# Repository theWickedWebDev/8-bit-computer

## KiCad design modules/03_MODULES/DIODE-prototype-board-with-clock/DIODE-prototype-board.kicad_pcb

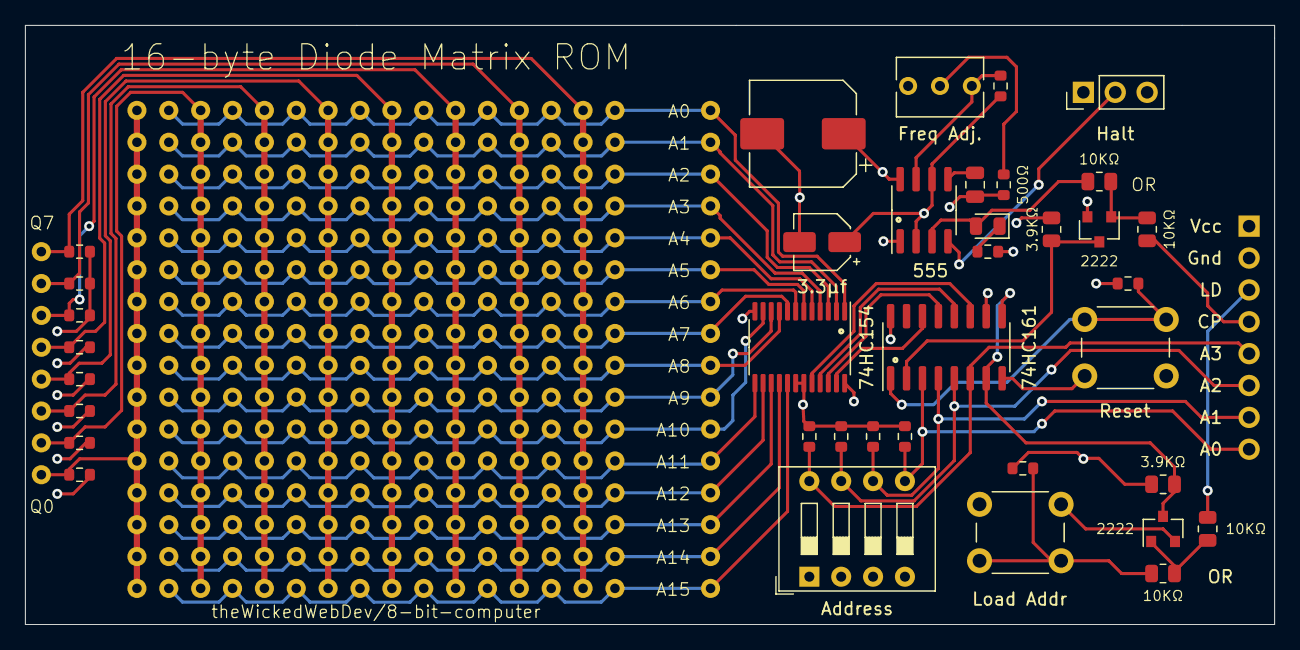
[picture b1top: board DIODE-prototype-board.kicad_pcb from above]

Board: 4 copper layers, 99.6 x 47.8 mm, 39 parts (1 on the bottom side), 49 nets.

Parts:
C1: C; C_0805_2012Metric
C2: CP1; CP_Elec_4x4.5
C3: CP1; CP_Elec_8x10
D1: LED; LED_0805_2012Metric
J1: Conn_01x08; PinHeader_1x08_P2.54mm_Vertical
Q1, Q2: PMBT2222; SOT-23
R1, R2, R3, R4, R5, R6, R7, R8, R9, R10, R11, R12, R13, R14, R15, R16, R17: R_US; R_0603_1608Metric
R18, R19, R21, R22: 10kohm; R_0805_2012Metric
R20, R23: 3.9kohm; R_0805_2012Metric
RV2: 3296W-1-203; Potentiometer_Bourns_3266Y_Vertical
SW1: SW_SPDT; PinHeader_1x03_P2.54mm_Vertical
SW2, SW4: SW_Push; SW_PUSH_6mm
SW3: SW_DIP_x04; SW_DIP_SPSTx04_Slide_9.78x12.34mm_W7.62mm_P2.54mm
U1: diode-matrix-8x16; diode-array-sockets
U2: TLC555xD; SOIC-8_3.9x4.9mm_P1.27mm
U3: 74LS154; TSSOP-24_4.4x7.8mm_P0.65mm
U4: 74LS161; SOIC-16_3.9x9.9mm_P1.27mm

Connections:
AUTO_CLOCK: D1.2, R18.1, U2.3
CLOCK: Q1.3, R20.2, U4.2
EXT_CLOCK: J1.4, R19.1
EXT_LOAD: J1.3, R21.1
GND: C2.2, C3.2, J1.2, Q1.2, Q2.2, R13.1, R14.1, R15.1, R16.1, R17.2, SW1.3, SW2.2, SW4.2, U2.1, U3.12, U3.18, U3.19, U4.8
LOAD: Q2.3, R23.2, U4.7, U4.9
unnamed: C1.1, U2.5
unnamed: C2.1, R5.2, U2.2, U2.6
unnamed: D1.1, R17.1
unnamed: J1.5, R16.2, SW3.8, U4.6
unnamed: J1.6, R15.2, SW3.7, U4.5
unnamed: J1.7, R14.2, SW3.6, U4.4
unnamed: J1.8, R13.2, SW3.5, U4.3
unnamed: Q1.1, R18.2, R19.2
unnamed: Q2.1, R21.2, R22.2
unnamed: R1.1, U1.1
unnamed: R2.1, U1.2
unnamed: R3.1, U1.3
unnamed: R4.1, U1.4
unnamed: R5.1, RV2.1, U2.7
unnamed: R6.1, U1.5
unnamed: R7.1, U1.6
unnamed: R8.1, U1.7
unnamed: R9.1, U1.8
unnamed: R10.1, RV2.2
unnamed: R11.1, SW2.1, U4.1
unnamed: R12.1, R22.1, SW4.1
unnamed: SW1.2, U2.4
unnamed: U1.9, U3.1
unnamed: U1.10, U3.2
unnamed: U1.11, U3.3
unnamed: U1.12, U3.4
unnamed: U1.13, U3.5
unnamed: U1.14, U3.6
unnamed: U1.15, U3.7
unnamed: U1.16, U3.8
unnamed: U1.17, U3.9
unnamed: U1.18, U3.10
unnamed: U1.19, U3.11
unnamed: U1.20, U3.13
unnamed: U1.21, U3.14
unnamed: U1.22, U3.15
unnamed: U1.23, U3.16
unnamed: U1.24, U3.17
unnamed: U3.20, U4.11
unnamed: U3.21, U4.12
unnamed: U3.22, U4.13
unnamed: U3.23, U4.14
VCC: C1.2, C3.1, J1.1, R1.2, R2.2, R3.2, R4.2, R6.2, R7.2, R8.2, R9.2, R10.2, R11.2, R12.2, R20.1, R23.1, SW1.1, SW3.1, SW3.2, SW3.3, SW3.4, U2.8, U3.24, U4.10, U4.16

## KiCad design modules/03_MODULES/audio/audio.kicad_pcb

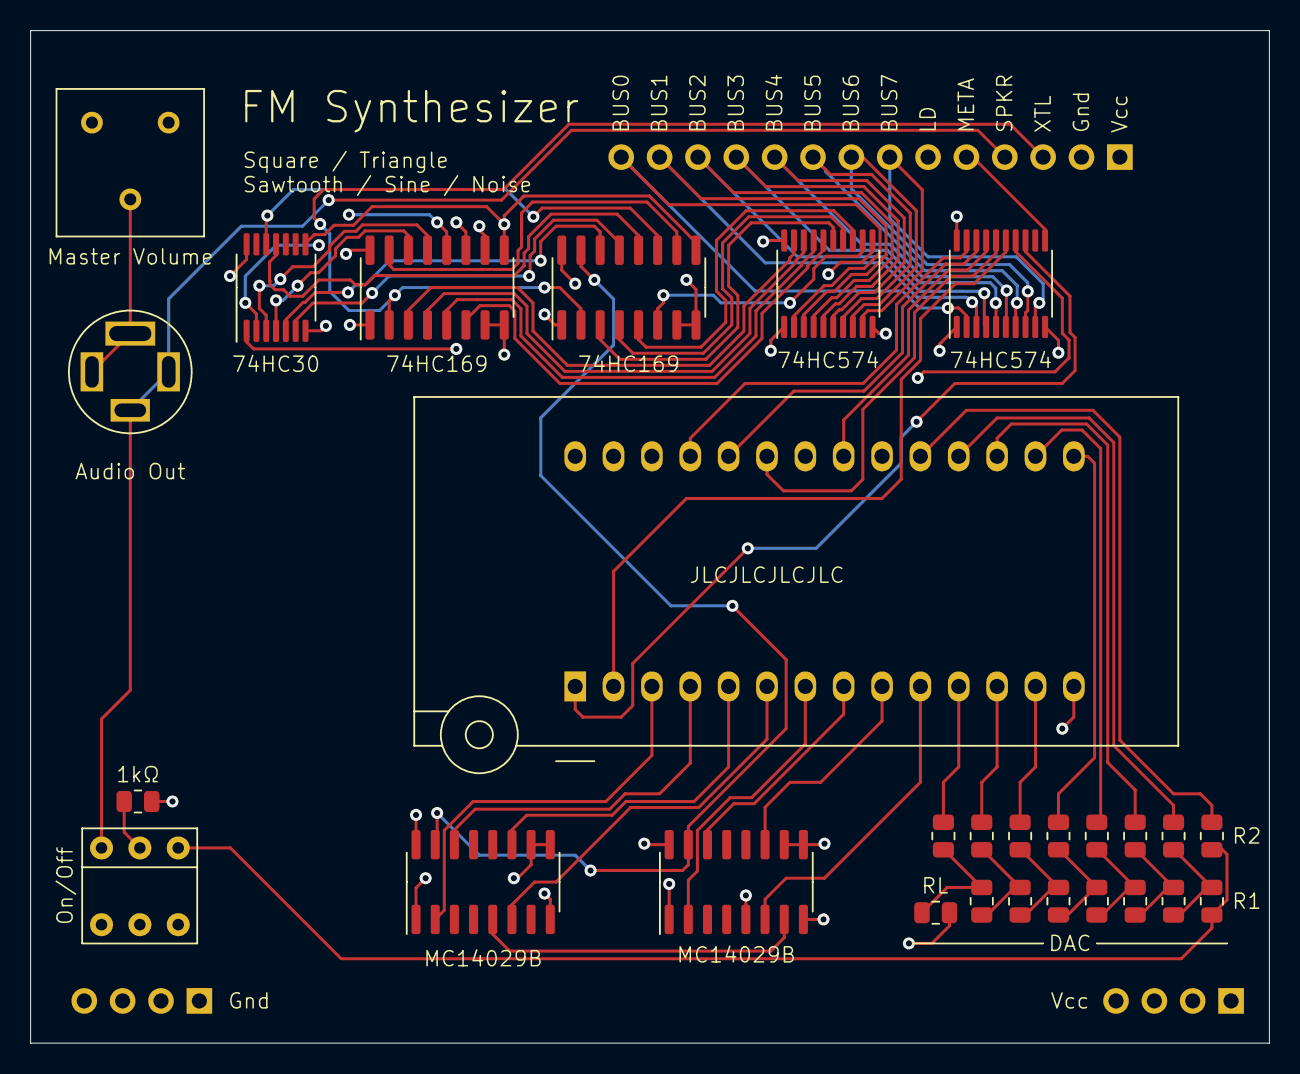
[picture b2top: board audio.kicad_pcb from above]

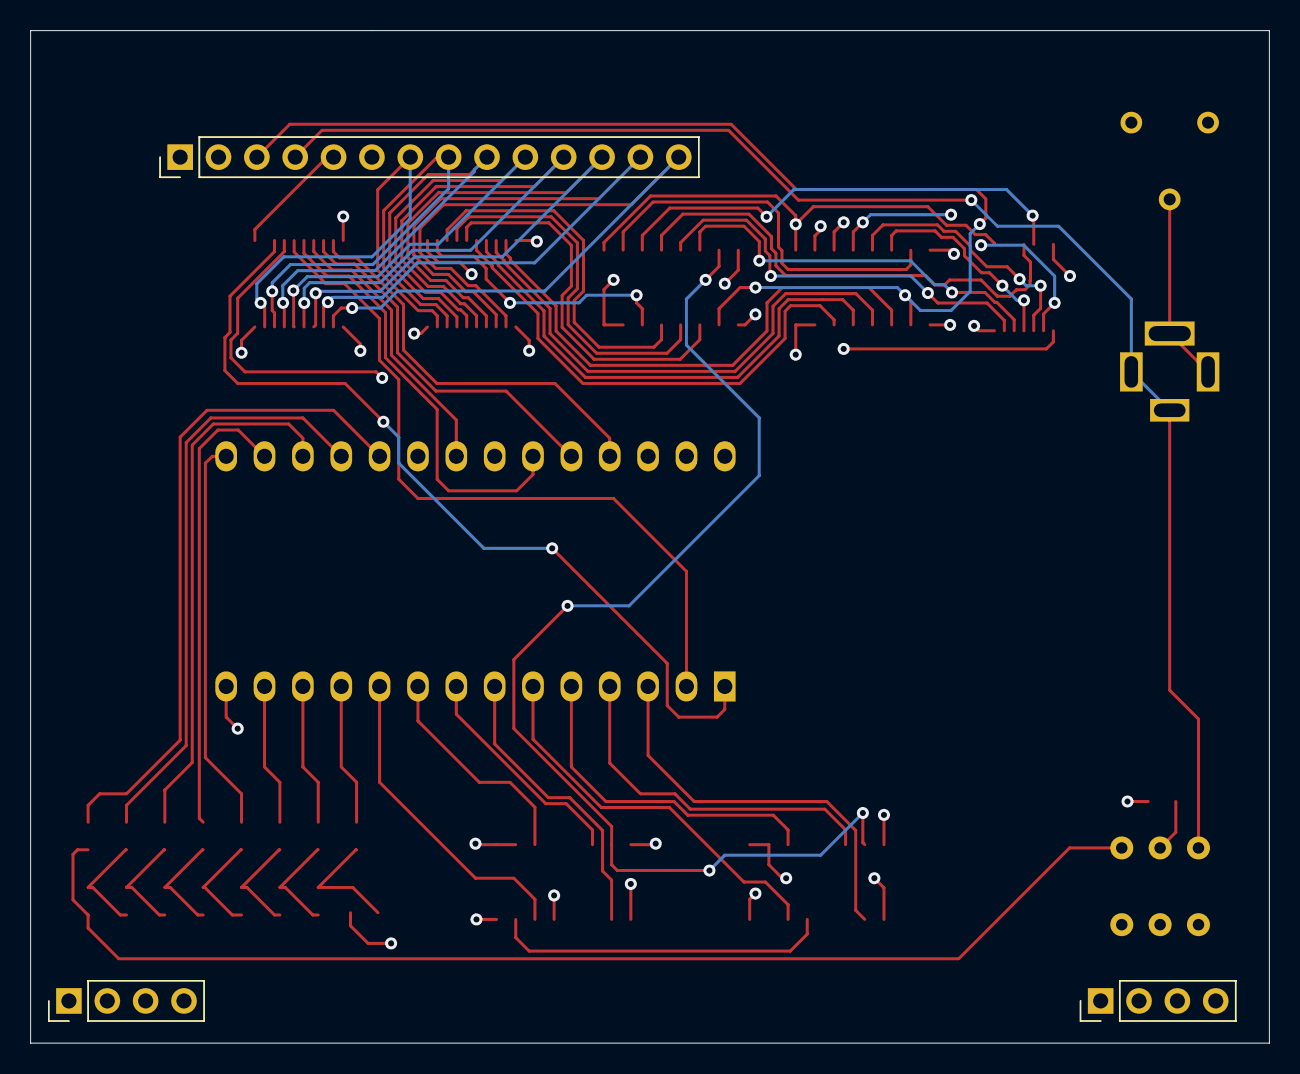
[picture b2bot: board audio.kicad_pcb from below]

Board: 4 copper layers, 82.0 x 67.1 mm, 31 parts (3 on the bottom side), 67 nets.

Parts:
J1: Conn_01x14; PinHeader_1x14_P2.54mm_Vertical
J3, J4: Conn_01x04; PinHeader_1x04_P2.54mm_Vertical
LS1: Speaker; 3.5mm_Audio_Jack-STEPHEN
R1, R2, R3, R4, R5, R6, R7, R8, R9, R10, R11, R12, R13, R14, R15, R16, R17: R_US; R_0805_2012Metric
RV1: R_POT_TRIM_US; Potentiometer_Bourns_3386F_Vertical
SW1: SW_DPDT_x2; THT-DPDT
U1, U2: 74LS574; TSSOP-20_4.4x6.5mm_P0.65mm
U3, U7: 74LS169; SOIC-16_3.9x9.9mm_P1.27mm
U4, U6: MC14029B; SOIC-16_3.9x9.9mm_P1.27mm
U5: 74LS30; TSSOP-14_4.4x5mm_P0.65mm
U8: 28C256; DIP_Socket-28_W11.9_W12.7_W15.24_W17.78_W18.5_3M_228-1277-0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

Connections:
/D1: R3.1, U8.12
/D2: R5.1, U8.13
/D3: R7.1, U8.15
/D4: R9.1, U8.16
/D5: R11.1, U8.17
/D6: R13.1, U8.18
/D7: R15.1, U8.19
/DO: R1.1, U8.11
/QDIVISION0: U2.19, U3.3
/QDIVISION1: U2.18, U3.4
/QDIVISION2: U2.17, U3.5
/QDIVISION3: U2.16, U3.6
/QDIVISION4: U2.15, U7.3
/QDIVISION5: U2.14, U7.4
/QDIVISION6: U2.13, U7.5
/QDIVISION7: U2.12, U7.6
A0: U4.6, U8.10
A1: U4.11, U8.9
A2: U4.14, U8.8
A3: U4.2, U8.7
A4: U6.6, U8.6
A5: U6.11, U8.5
A6: U6.14, U8.4
A7: U6.2, U8.3
A8: U1.19, U8.25
A9: U1.18, U8.24
A10: U1.17, U8.21
A11: U1.16, U8.23
A12: U1.15, U8.2
A13: U1.14, U8.26
A14: U1.13, U8.1
CRYSTAL_OSCILLATOR_IN: J1.3, U3.2, U7.2
DATABUS0: J1.14, U1.2, U2.2
DATABUS1: J1.13, U1.3, U2.3
DATABUS2: J1.12, U1.4, U2.4
DATABUS3: J1.11, U1.5, U2.5
DATABUS4: J1.10, U1.6, U2.6
DATABUS5: J1.9, U1.7, U2.7
DATABUS6: J1.8, U1.8, U2.8
DATABUS7: J1.7, U1.9, U2.9
FREQ0: U3.14, U5.4
FREQ1: U3.13, U5.3
FREQ2: U3.12, U5.2
FREQ3: U3.11, U5.1
FREQ4: U5.5, U7.14
FREQ5: U5.6, U7.13
FREQ6: U5.11, U7.12
FREQ7: U5.12, U7.11
FREQUENCY_CLOCK_PULSE: U4.15, U6.15, U7.15
GND: J1.2, J4.1, J4.2, J4.3, J4.4, R16.2, R17.1, RV1.3, U1.1, U1.10, U2.1, U2.10, U3.1, U3.7, U3.8, U3.10, U4.1, U4.5, U4.8, U5.7, U6.1, U6.8, U7.1, U7.7, U7.8, U8.14, U8.20, U8.22
LOAD_DIVISION: J1.6, U2.11
LOAD_META: J1.5, U1.11
unnamed: LS1.R1, LS1.R2, RV1.2
unnamed: R1.2, R2.2, R16.1
unnamed: R2.1, R3.2, R4.2
unnamed: R4.1, R5.2, R6.2
unnamed: R6.1, R7.2, R8.2
unnamed: R10.1, R11.2, R12.2
unnamed: R8.1, R9.2, R10.2
unnamed: R12.1, R13.2, R14.2
unnamed: R14.1, R15.2, SW1.1
unnamed: R17.2, SW1.3
unnamed: U3.15, U7.10
unnamed: U4.7, U6.5
SPEAKER_OUT: J1.4, LS1.S, LS1.T, SW1.2
VCC: J1.1, J3.1, J3.2, J3.3, J3.4, U1.20, U2.20, U3.16, U4.9, U4.10, U4.16, U5.14, U6.9, U6.10, U6.16, U7.16, U8.27, U8.28
~ENABLE_COUNTER_LOAD: U3.9, U5.8, U7.9

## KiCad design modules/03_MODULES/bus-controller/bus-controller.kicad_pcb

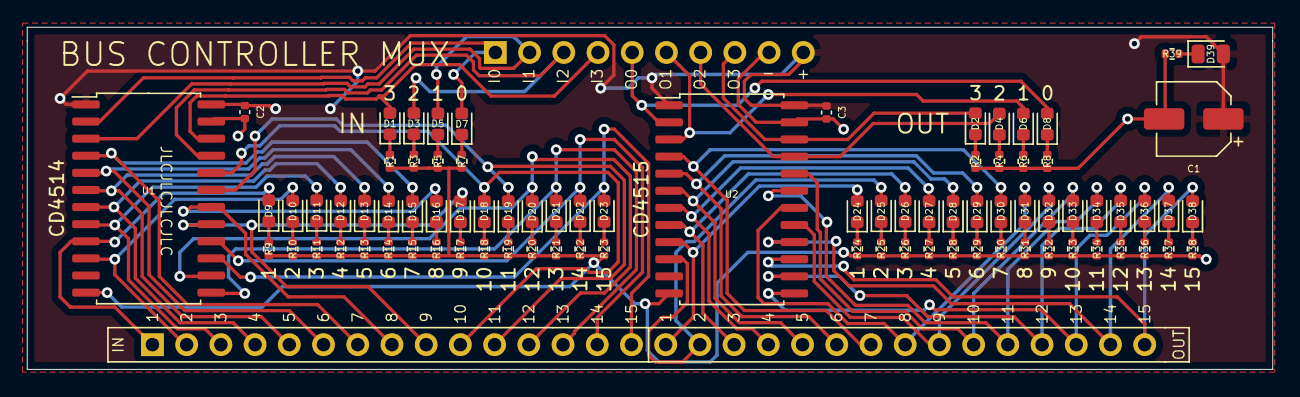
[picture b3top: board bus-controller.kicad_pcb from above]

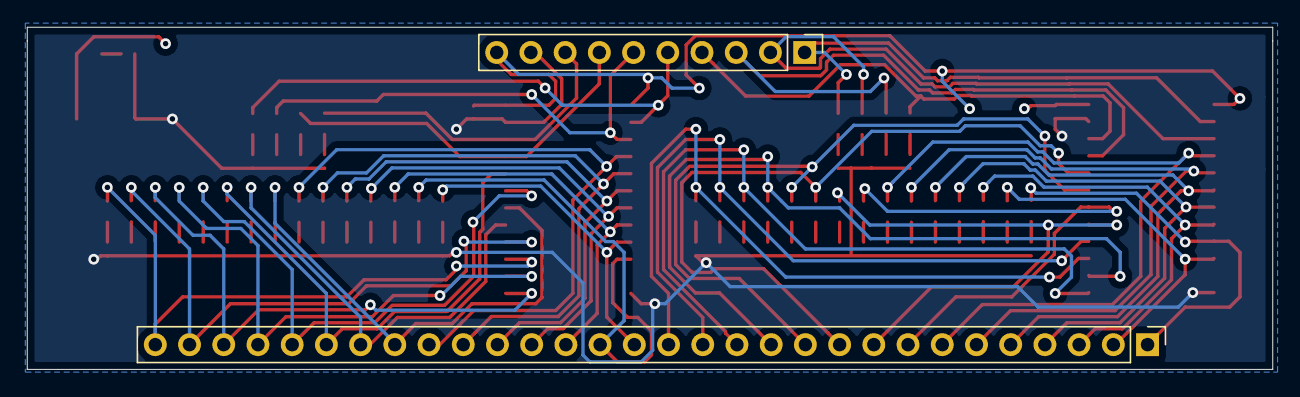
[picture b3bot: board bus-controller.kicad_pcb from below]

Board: 2 copper layers, 92.5 x 25.4 mm, 85 parts (2 on the bottom side), 79 nets.

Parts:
C1: SMD-ECAP-5x5.8; CP_Elec_5x5.8
C2, C3: CL05A106MQ5NUNC; C_0402_1005Metric
D1, D2, D3, D4, D5, D6, D7, D8: 19-217/BHC-ZL1M2RY/3T; LED_0603_1608Metric
D9, D10, D11, D12, D13, D14, D15, D16, D17, D18, D19, D20, D21, D22, D23, D24, D25, D26, D27, D28, D29, D30, D31, D32, D33, D34, D35, D36, D37, D38: 19-217/GHC-YR1S2/3T; LED_0603_1608Metric
D39: NCD0805R1; LED_0805_2012Metric
J1: Conn_01x30; PinHeader_1x30_P2.54mm_Vertical
J2: Conn_01x10; PinHeader_1x10_P2.54mm_Vertical
R1, R2, R3, R4, R5, R6, R7, R8, R9, R10, R11, R12, R13, R14, R15, R16, R17, R18, R19, R20, R21, R22, R23, R24, R25, R26, R27, R28, R29, R30, R31, R32, R33, R34, R35, R36, R37, R38, R39: 0402WGF1001TCE; R_0402_1005Metric
U1: CD4514BM96; SOIC-24W_7.5x15.4mm_P1.27mm
U2: CD4515BM96; SOIC-24W_7.5x15.4mm_P1.27mm

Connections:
GND: C1.2, C2.2, C3.2, J2.9, R1.2, R2.2, R3.2, R4.2, R5.2, R6.2, R7.2, R8.2, R9.2, R10.2, R11.2, R12.2, R13.2, R14.2, R15.2, R16.2, R17.2, R18.2, R19.2, R20.2, R21.2, R22.2, R23.2, R24.2, R25.2, R26.2, R27.2, R28.2, R29.2, R30.2, R31.2, R32.2, R33.2, R34.2, R35.2, R36.2, R37.2, R38.2, R39.2, U1.12, U1.23, U2.12, U2.23
I1: D9.2, J1.1, U1.9
I2: D10.2, J1.2, U1.10
I3: D11.2, J1.3, U1.8
I4: D12.2, J1.4, U1.7
I5: D13.2, J1.5, U1.6
I6: D14.2, J1.6, U1.5
I7: D15.2, J1.7, U1.4
I8: D16.2, J1.8, U1.18
I9: D17.2, J1.9, U1.17
I10: D18.2, J1.10, U1.20
I11: D19.2, J1.11, U1.19
I12: D20.2, J1.12, U1.14
I13: D21.2, J1.13, U1.13
I14: D22.2, J1.14, U1.16
I15: D23.2, J1.15, U1.15
IS0: D7.2, J2.1, U1.2
IS1: D5.2, J2.2, U1.3
IS2: D3.2, J2.3, U1.21
IS3: D1.2, J2.4, U1.22
unnamed: D1.1, R1.1
unnamed: D2.1, R2.1
unnamed: D3.1, R3.1
unnamed: D4.1, R4.1
unnamed: D5.1, R5.1
unnamed: D6.1, R6.1
unnamed: D7.1, R7.1
unnamed: D8.1, R8.1
unnamed: D9.1, R9.1
unnamed: D10.1, R10.1
unnamed: D11.1, R11.1
unnamed: D12.1, R12.1
unnamed: D13.1, R13.1
unnamed: D14.1, R14.1
unnamed: D15.1, R15.1
unnamed: D16.1, R16.1
unnamed: D17.1, R17.1
unnamed: D18.1, R18.1
unnamed: D19.1, R19.1
unnamed: D20.1, R20.1
unnamed: D21.1, R21.1
unnamed: D22.1, R22.1
unnamed: D23.1, R23.1
unnamed: D24.1, R24.1
unnamed: D25.1, R25.1
unnamed: D26.1, R26.1
unnamed: D27.1, R27.1
unnamed: D28.1, R28.1
unnamed: D29.1, R29.1
unnamed: D30.1, R30.1
unnamed: D31.1, R31.1
unnamed: D32.1, R32.1
unnamed: D33.1, R33.1
unnamed: D34.1, R34.1
unnamed: D35.1, R35.1
unnamed: D36.1, R36.1
unnamed: D37.1, R37.1
unnamed: D38.1, R38.1
unnamed: D39.1, R39.1
O1: D24.2, J1.16, U2.9
O2: D25.2, J1.17, U2.10
O3: D26.2, J1.18, U2.8
O4: D27.2, J1.19, U2.7
O5: D28.2, J1.20, U2.6
O6: D29.2, J1.21, U2.5
O7: D30.2, J1.22, U2.4
O8: D31.2, J1.23, U2.18
O9: D32.2, J1.24, U2.17
O10: D33.2, J1.25, U2.20
O11: D34.2, J1.26, U2.19
O12: D35.2, J1.27, U2.14
O13: D36.2, J1.28, U2.13
O14: D37.2, J1.29, U2.16
O15: D38.2, J1.30, U2.15
OS0: D8.2, J2.5, U2.2
OS1: D6.2, J2.6, U2.3
OS2: D4.2, J2.7, U2.21
OS3: D2.2, J2.8, U2.22
VCC: C1.1, C2.1, C3.1, D39.2, J2.10, U1.1, U1.24, U2.1, U2.24

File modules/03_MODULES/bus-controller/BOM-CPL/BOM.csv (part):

Designator,Value,LibPart,Footprint,Datasheet,C,Color,Description,JLCPCB,,
C1,SMD-ECAP-5x5.8,Device:CP1_Small,Capacitor_SMD:CP_Elec_5x5.8,https://datasheet.lcsc.com/lcsc/1810010225_Lelon-VZS101M1ATR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,100µf,,"- - 5mm 100uF 10V -45℃~+105℃ ±20% 5.8mm 2000hrs 105℃ SMD,5x5.8mm Aluminum Electrolytic Capacitors - SMD ROHS",C140924,,
C2,CL05A106MQ5NUNC,Device:C,Capacitor_SMD:C_0402_1005Metric,https://datasheet.lcsc.com/lcsc/1810191215_Samsung-Electro-M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,10µf,,X5R 6.3V ±20% 10uF 0402 Multilayer Ceramic Capacitors MLCC - SMD/SMT ROHS,C15525,,
C3,CL05A106MQ5NUNC,Device:C,Capacitor_SMD:C_0402_1005Metric,https://datasheet.lcsc.com/lcsc/1810191215_Samsung-Electro-M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,10µf,,X5R 6.3V ±20% 10uF 0402 Multilayer Ceramic Capacitors MLCC - SMD/SMT ROHS,C15525,,
D1,19-217/BHC-ZL1M2RY/3T,Device:LED,LED_SMD:LED_0603_1608Metric,https://datasheet.lcsc.com/lcsc/1811101510_Everlight-Elec-19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,,BLU,,C72041,,
D2,19-217/BHC-ZL1M2RY/3T,Device:LED,LED_SMD:LED_0603_1608Metric,https://datasheet.lcsc.com/lcsc/1811101510_Everlight-Elec-19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,,BLU,,C72041,,
D3,19-217/BHC-ZL1M2RY/3T,Device:LED,LED_SMD:LED_0603_1608Metric,https://datasheet.lcsc.com/lcsc/1811101510_Everlight-Elec-19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,,BLU,,C72041,,
D4,19-217/BHC-ZL1M2RY/3T,Device:LED,LED_SMD:LED_0603_1608Metric,https://datasheet.lcsc.com/lcsc/1811101510_Everlight-Elec-19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,,BLU,,C72041,,
D5,19-217/BHC-ZL1M2RY/3T,Device:LED,LED_SMD:LED_0603_1608Metric,https://datasheet.lcsc.com/lcsc/1811101510_Everlight-Elec-19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,,BLU,,C72041,,
D6,19-217/BHC-ZL1M2RY/3T,Device:LED,LED_SMD:LED_0603_1608Metric,https://datasheet.lcsc.com/lcsc/1811101510_Everlight-Elec-19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,,BLU,,C72041,,
D7,19-217/BHC-ZL1M2RY/3T,Device:LED,LED_SMD:LED_0603_1608Metric,https://datasheet.lcsc.com/lcsc/1811101510_Everlight-Elec-19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,,BLU,,C72041,,
D8,19-217/BHC-ZL1M2RY/3T,Device:LED,LED_SMD:LED_0603_1608Metric,https://datasheet.lcsc.com/lcsc/1811101510_Everlight-Elec-19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,,BLU,,C72041,,
D9,19-217/GHC-YR1S2/3T,Device:LED,LED_SMD:LED_0603_1608Metric,https://datasheet.lcsc.com/lcsc/1811101510_Everlight-Elec-19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,,GRN,,C72043,,
D10,19-217/GHC-YR1S2/3T,Device:LED,LED_SMD:LED_0603_1608Metric,https://datasheet.lcsc.com/lcsc/1811101510_Everlight-Elec-19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,,GRN,,C72043,,
D11,19-217/GHC-YR1S2/3T,Device:LED,LED_SMD:LED_0603_1608Metric,https://datasheet.lcsc.com/lcsc/1811101510_Everlight-Elec-19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,,GRN,,C72043,,
D12,19-217/GHC-YR1S2/3T,Device:LED,LED_SMD:LED_0603_1608Metric,https://datasheet.lcsc.com/lcsc/1811101510_Everlight-Elec-19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,,GRN,,C72043,,
D13,19-217/GHC-YR1S2/3T,Device:LED,LED_SMD:LED_0603_1608Metric,https://datasheet.lcsc.com/lcsc/1811101510_Everlight-Elec-19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,,GRN,,C72043,,
D14,19-217/GHC-YR1S2/3T,Device:LED,LED_SMD:LED_0603_1608Metric,https://datasheet.lcsc.com/lcsc/1811101510_Everlight-Elec-19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,,GRN,,C72043,,
D15,19-217/GHC-YR1S2/3T,Device:LED,LED_SMD:LED_0603_1608Metric,https://datasheet.lcsc.com/lcsc/1811101510_Everlight-Elec-19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,,GRN,,C72043,,
D16,19-217/GHC-YR1S2/3T,Device:LED,LED_SMD:LED_0603_1608Metric,https://datasheet.lcsc.com/lcsc/1811101510_Everlight-Elec-19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,,GRN,,C72043,,
D17,19-217/GHC-YR1S2/3T,Device:LED,LED_SMD:LED_0603_1608Metric,https://datasheet.lcsc.com/lcsc/1811101510_Everlight-Elec-19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,,GRN,,C72043,,
D18,19-217/GHC-YR1S2/3T,Device:LED,LED_SMD:LED_0603_1608Metric,https://datasheet.lcsc.com/lcsc/1811101510_Everlight-Elec-19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,,GRN,,C72043,,
D19,19-217/GHC-YR1S2/3T,Device:LED,LED_SMD:LED_0603_1608Metric,https://datasheet.lcsc.com/lcsc/1811101510_Everlight-Elec-19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,,GRN,,C72043,,
D20,19-217/GHC-YR1S2/3T,Device:LED,LED_SMD:LED_0603_1608Metric,https://datasheet.lcsc.com/lcsc/1811101510_Everlight-Elec-19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,,GRN,,C72043,,
D21,19-217/GHC-YR1S2/3T,Device:LED,LED_SMD:LED_0603_1608Metric,https://datasheet.lcsc.com/lcsc/1811101510_Everlight-Elec-19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,,GRN,,C72043,,
D22,19-217/GHC-YR1S2/3T,Device:LED,LED_SMD:LED_0603_1608Metric,https://datasheet.lcsc.com/lcsc/1811101510_Everlight-Elec-19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,,GRN,,C72043,,
D23,19-217/GHC-YR1S2/3T,Device:LED,LED_SMD:LED_0603_1608Metric,https://datasheet.lcsc.com/lcsc/1811101510_Everlight-Elec-19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,,GRN,,C72043,,
D24,19-217/GHC-YR1S2/3T,Device:LED,LED_SMD:LED_0603_1608Metric,https://datasheet.lcsc.com/lcsc/1811101510_Everlight-Elec-19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,,GRN,,C72043,,
D25,19-217/GHC-YR1S2/3T,Device:LED,LED_SMD:LED_0603_1608Metric,https://datasheet.lcsc.com/lcsc/1811101510_Everlight-Elec-19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,,GRN,,C72043,,
D26,19-217/GHC-YR1S2/3T,Device:LED,LED_SMD:LED_0603_1608Metric,https://datasheet.lcsc.com/lcsc/1811101510_Everlight-Elec-19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,,GRN,,C72043,,
D27,19-217/GHC-YR1S2/3T,Device:LED,LED_SMD:LED_0603_1608Metric,https://datasheet.lcsc.com/lcsc/1811101510_Everlight-Elec-19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,,GRN,,C72043,,
D28,19-217/GHC-YR1S2/3T,Device:LED,LED_SMD:LED_0603_1608Metric,https://datasheet.lcsc.com/lcsc/1811101510_Everlight-Elec-19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,,GRN,,C72043,,
D29,19-217/GHC-YR1S2/3T,Device:LED,LED_SMD:LED_0603_1608Metric,https://datasheet.lcsc.com/lcsc/1811101510_Everlight-Elec-19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,,GRN,,C72043,,
D30,19-217/GHC-YR1S2/3T,Device:LED,LED_SMD:LED_0603_1608Metric,https://datasheet.lcsc.com/lcsc/1811101510_Everlight-Elec-19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,,GRN,,C72043,,
D31,19-217/GHC-YR1S2/3T,Device:LED,LED_SMD:LED_0603_1608Metric,https://datasheet.lcsc.com/lcsc/1811101510_Everlight-Elec-19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,,GRN,,C72043,,
D32,19-217/GHC-YR1S2/3T,Device:LED,LED_SMD:LED_0603_1608Metric,https://datasheet.lcsc.com/lcsc/1811101510_Everlight-Elec-19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,,GRN,,C72043,,
D33,19-217/GHC-YR1S2/3T,Device:LED,LED_SMD:LED_0603_1608Metric,https://datasheet.lcsc.com/lcsc/1811101510_Everlight-Elec-19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,,GRN,,C72043,,
D34,19-217/GHC-YR1S2/3T,Device:LED,LED_SMD:LED_0603_1608Metric,https://datasheet.lcsc.com/lcsc/1811101510_Everlight-Elec-19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,,GRN,,C72043,,
D35,19-217/GHC-YR1S2/3T,Device:LED,LED_SMD:LED_0603_1608Metric,https://datasheet.lcsc.com/lcsc/1811101510_Everlight-Elec-19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,,GRN,,C72043,,
D36,19-217/GHC-YR1S2/3T,Device:LED,LED_SMD:LED_0603_1608Metric,https://datasheet.lcsc.com/lcsc/1811101510_Everlight-Elec-19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,,GRN,,C72043,,
D37,19-217/GHC-YR1S2/3T,Device:LED,LED_SMD:LED_0603_1608Metric,https://datasheet.lcsc.com/lcsc/1811101510_Everlight-Elec-19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,,GRN,,C72043,,
D38,19-217/GHC-YR1S2/3T,Device:LED,LED_SMD:LED_0603_1608Metric,https://datasheet.lcsc.com/lcsc/1811101510_Everlight-Elec-19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,,GRN,,C72043,,
D39,NCD0805R1,Device:LED,LED_SMD:LED_0805_2012Metric,https://datasheet.lcsc.com/lcsc/2008201032_Foshan-NationStar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,,RED,,C84256,,
J1,Conn_01x30,Connector_Generic:Conn_01x30,Connector_PinHeader_2.54mm:PinHeader_1x30_P2.54mm_Vertical,~,,,,,,
J2,Conn_01x10,Connector_Generic:Conn_01x10,Connector_PinHeader_2.54mm:PinHeader_1x10_P2.54mm_Vertical,~,,,,,,
R1,0402WGF1001TCE,Device:R_Small_US,Resistor_SMD:R_0402_1005Metric,https://datasheet.lcsc.com/lcsc/1811132311_UNI-ROYAL-Uniroya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,,,±1% 1/16W ±100ppm/℃ 1kΩ 0402 Chip Resistor - Surface Mount ROHS,C11702,,
R2,0402WGF1001TCE,Device:R_Small_US,Resistor_SMD:R_0402_1005Metric,https://datasheet.lcsc.com/lcsc/1811132311_UNI-ROYAL-Uniroya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,,,±1% 1/16W ±100ppm/℃ 1kΩ 0402 Chip Resistor - Surface Mount ROHS,C11702,,
R3,0402WGF1001TCE,Device:R_Small_US,Resistor_SMD:R_0402_1005Metric,https://datasheet.lcsc.com/lcsc/1811132311_UNI-ROYAL-Uniroya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,,,±1% 1/16W ±100ppm/℃ 1kΩ 0402 Chip Resistor - Surface Mount ROHS,C11702,,
R4,0402WGF1001TCE,Device:R_Small_US,Resistor_SMD:R_0402_1005Metric,https://datasheet.lcsc.com/lcsc/1811132311_UNI-ROYAL-Uniroya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,,,±1% 1/16W ±100ppm/℃ 1kΩ 0402 Chip Resistor - Surface Mount ROHS,C11702,,
R5,0402WGF1001TCE,Device:R_Small_US,Resistor_SMD:R_0402_1005Metric,https://datasheet.lcsc.com/lcsc/1811132311_UNI-ROYAL-Uniroya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,,,±1% 1/16W ±100ppm/℃ 1kΩ 0402 Chip Resistor - Surface Mount ROHS,C11702,,
R6,0402WGF1001TCE,Device:R_Small_US,Resistor_SMD:R_0402_1005Metric,https://datasheet.lcsc.com/lcsc/1811132311_UNI-ROYAL-Uniroya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,,,±1% 1/16W ±100ppm/℃ 1kΩ 0402 Chip Resistor - Surface Mount ROHS,C11702,,
R7,0402WGF1001TCE,Device:R_Small_US,Resistor_SMD:R_0402_1005Metric,https://datasheet.lcsc.com/lcsc/1811132311_UNI-ROYAL-Uniroya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,,,±1% 1/16W ±100ppm/℃ 1kΩ 0402 Chip Resistor - Surface Mount ROHS,C11702,,
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
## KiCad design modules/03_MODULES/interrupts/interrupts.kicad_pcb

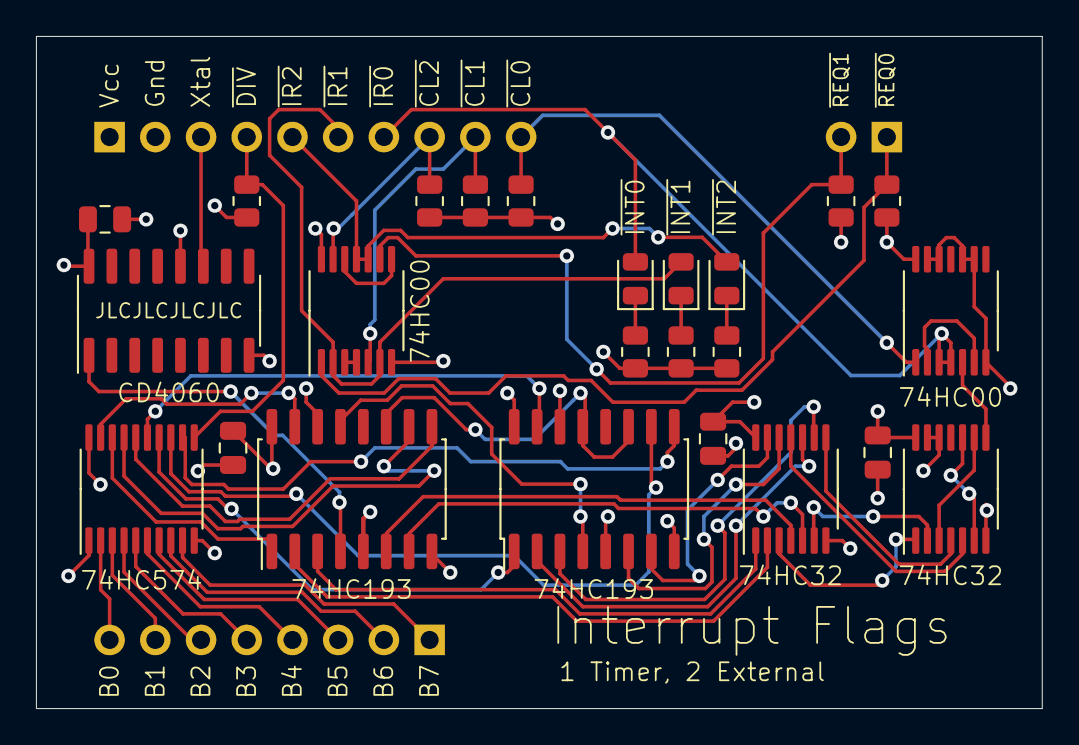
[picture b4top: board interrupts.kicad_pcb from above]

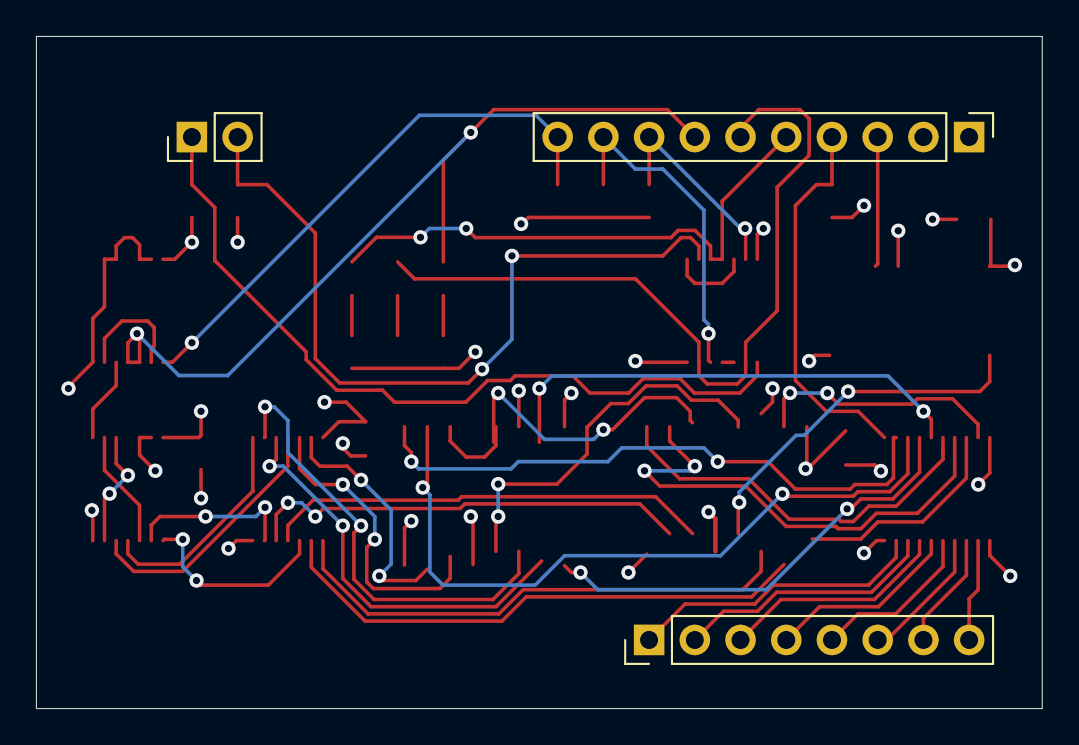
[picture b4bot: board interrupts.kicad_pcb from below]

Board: 4 copper layers, 55.9 x 37.3 mm, 27 parts (3 on the bottom side), 52 nets.

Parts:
C1, C2, C3, C4: C; C_0805_2012Metric
D1, D2, D3: LED; LED_0805_2012Metric
J1: Conn_01x10; PinHeader_1x10_P2.54mm_Vertical
J2: Conn_01x08; PinHeader_1x08_P2.54mm_Vertical
J3: Conn_01x02; PinHeader_1x02_P2.54mm_Vertical
R1, R2, R3, R4, R5, R6, R7, R8, R9: R_US; R_0805_2012Metric
U6: CD4060; SOIC-16_3.9x9.9mm_P1.27mm
U7: 74LS574; TSSOP-20_4.4x6.5mm_P0.65mm
U8, U9: 74LS193; SO-16_5.3x10.2mm_P1.27mm
U10, U11: 74LS32; TSSOP-14_4.4x5mm_P0.65mm
U12, U13: 74LS00; TSSOP-14_4.4x5mm_P0.65mm

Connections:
/BUS0: J2.8, U7.2
/BUS1: J2.7, U7.3
/BUS2: J2.6, U7.4
/BUS3: J2.5, U7.5
/BUS4: J2.4, U7.6
/BUS5: J2.3, U7.7
/BUS6: J2.2, U7.8
/BUS7: J2.1, U7.9
GND: C1.2, C2.2, C3.2, C4.2, J1.2, R1.2, R2.2, R3.2, U6.8, U6.12, U7.1, U7.10, U8.8, U8.14, U9.8, U9.14, U10.7, U11.7, U11.12, U11.13, U12.7, U12.9, U12.10, U12.12, U12.13, U13.7
unnamed: D1.1, R1.1
unnamed: D2.1, R2.1
unnamed: D3.1, R3.1
unnamed: U6.1, U8.4
unnamed: U7.12, U9.9
unnamed: U7.13, U9.10
unnamed: U7.14, U9.1
unnamed: U7.15, U9.15
unnamed: U7.16, U8.9
unnamed: U7.17, U8.10
unnamed: U7.18, U8.1
unnamed: U7.19, U8.15
unnamed: U8.11, U9.11, U9.13
unnamed: U8.13, U9.4
unnamed: U8.3, U10.1
unnamed: U8.2, U10.2
unnamed: U10.3, U11.1
unnamed: U8.6, U10.4
unnamed: U8.7, U10.5
unnamed: U10.6, U11.2
unnamed: U10.8, U11.4
unnamed: U9.3, U10.9
unnamed: U9.2, U10.10
unnamed: U10.11, U11.5
unnamed: U9.6, U10.12
unnamed: U9.7, U10.13
unnamed: U11.3, U11.9
unnamed: U11.8, U12.5
unnamed: U11.6, U11.10
unnamed: U12.2, U12.6
unnamed: U13.3, U13.4
unnamed: U13.8, U13.12
VCC: C1.1, C2.1, C3.1, C4.1, J1.1, R4.2, R5.2, R6.2, R7.2, R8.2, R9.2, U6.16, U7.20, U8.5, U8.16, U9.5, U9.16, U10.14, U11.14, U12.14, U13.14
XTAL: J1.3, U6.11
~INTCLR0: J1.10, R4.1, U12.1
~INTCLR1: J1.9, R5.1, U13.5
~INTCLR2: J1.8, R6.1, U13.13
~INTREQ0: D1.2, J1.7, U12.3, U12.4
~INTREQ1: D2.2, J1.6, U13.2, U13.6
~INTREQ2: D3.2, J1.5, U13.10, U13.11
~INT_REQ_0: J3.1, R7.1, U13.1
~INT_REQ_1: J3.2, R8.1, U13.9
~LATCH_TIMER_INTERRUPT_DIVISION: J1.4, R9.1, U7.11

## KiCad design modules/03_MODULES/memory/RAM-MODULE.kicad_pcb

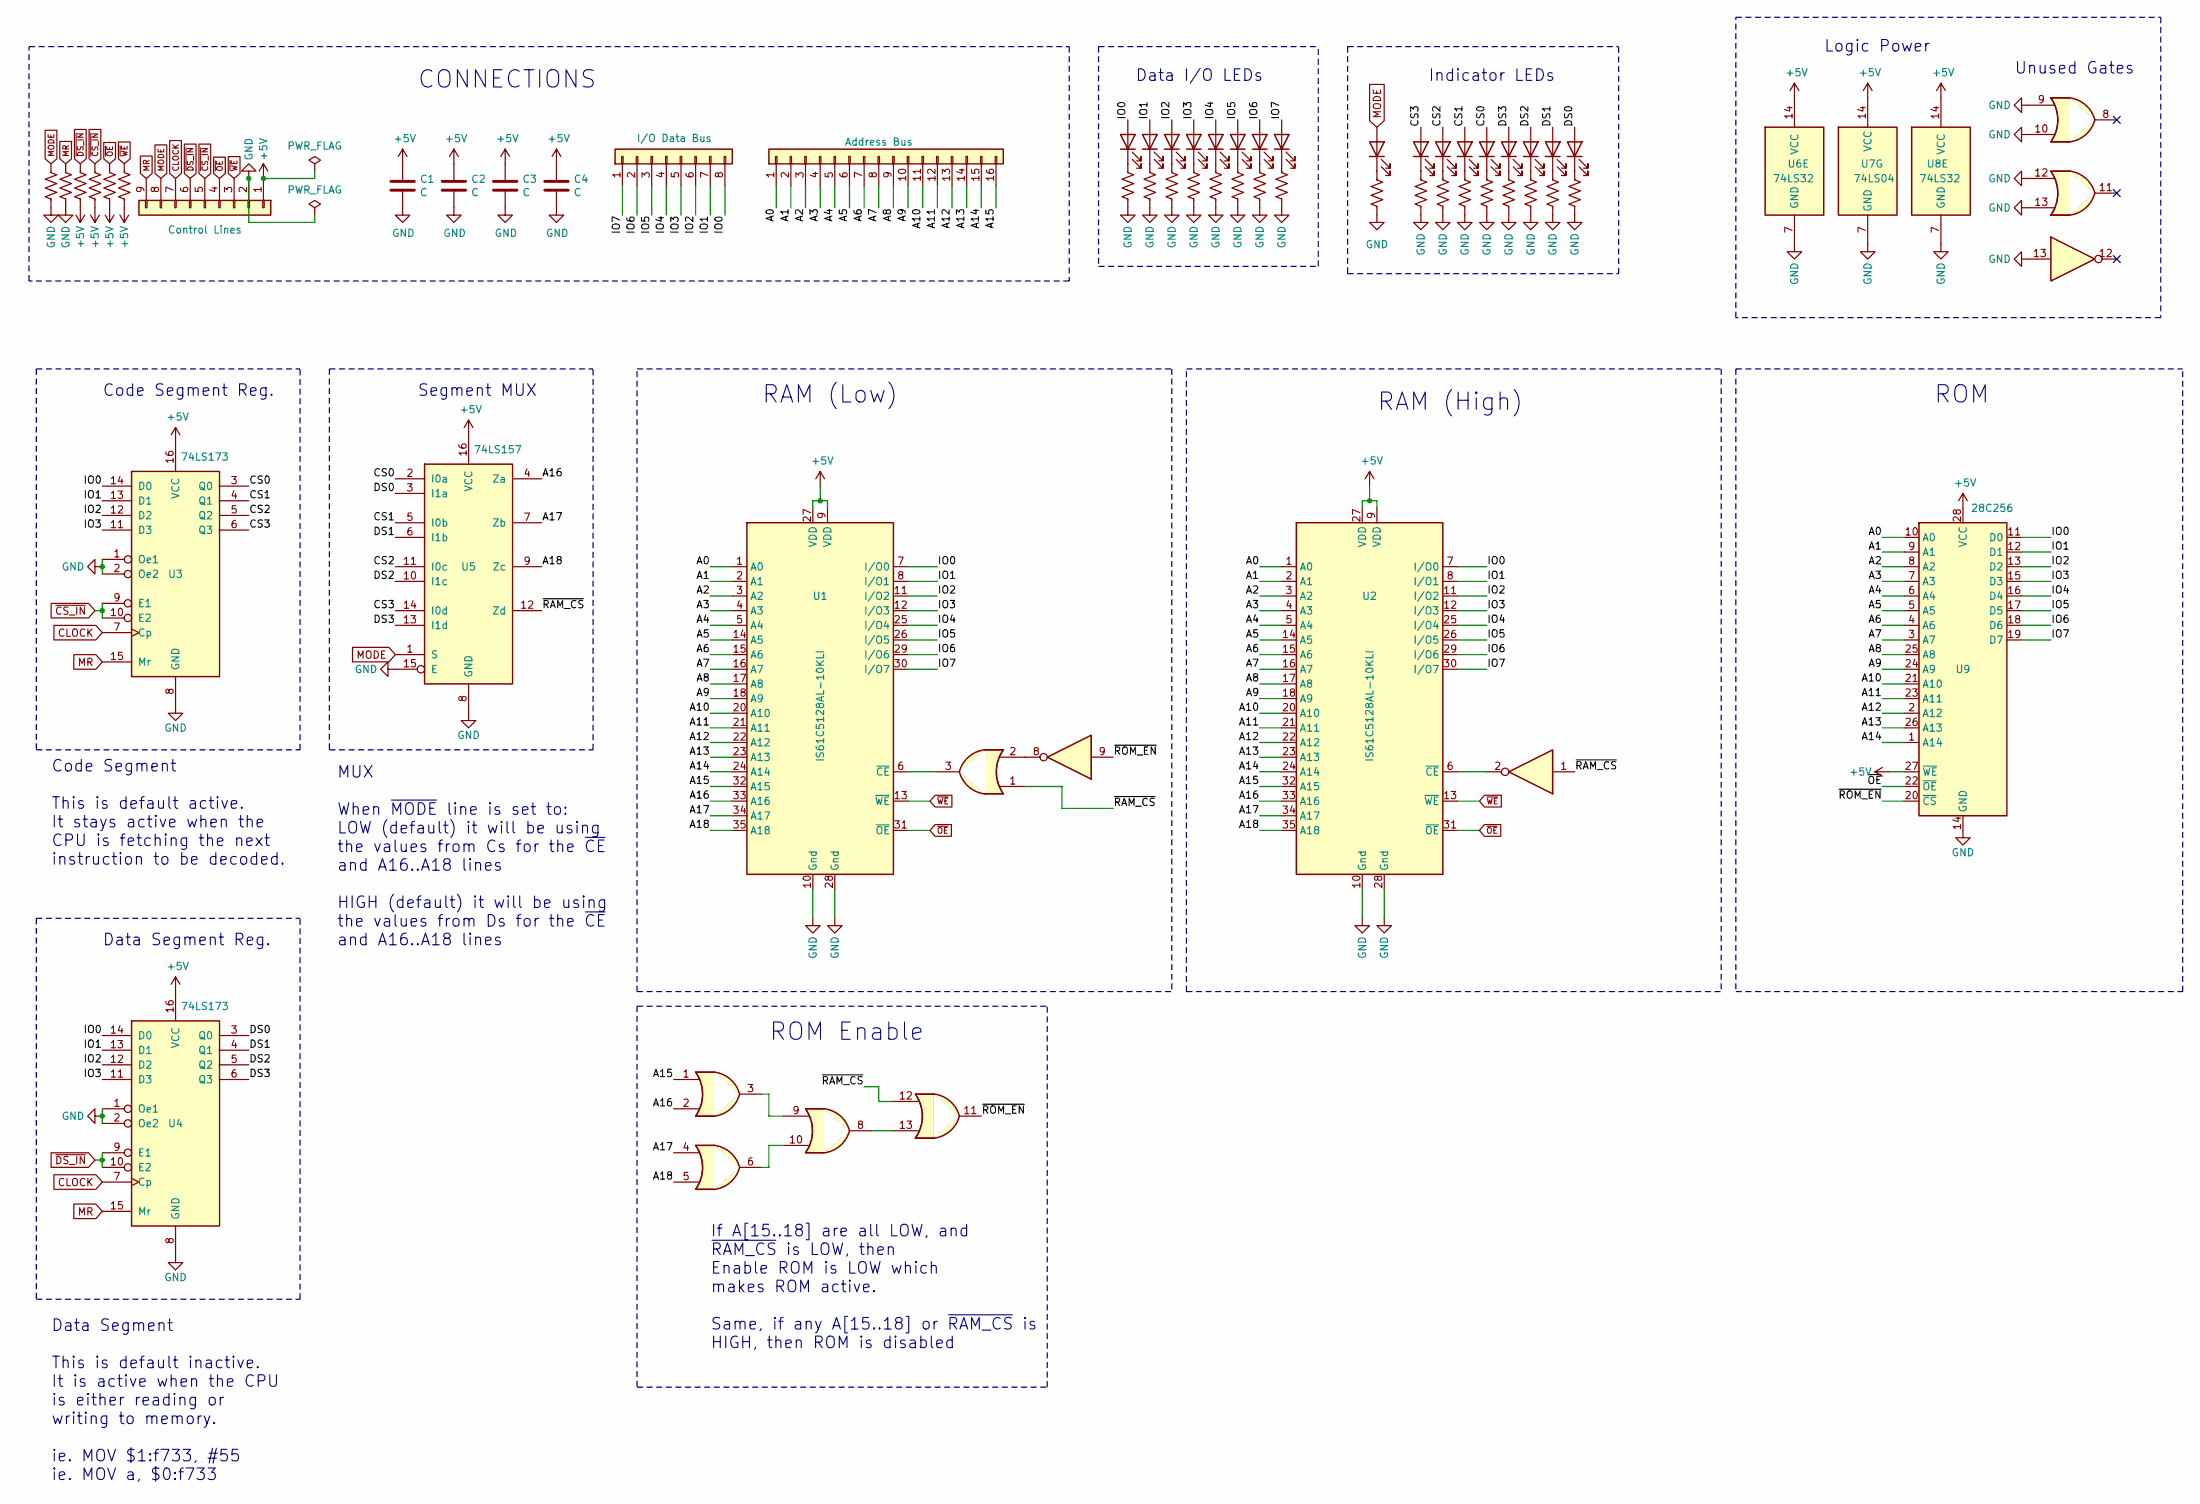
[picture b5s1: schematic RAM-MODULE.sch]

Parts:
C1, C2, C3, C4: C; C_0805_2012Metric
D1, D2, D3, D4, D5, D6, D7, D8, D9, D10, D11, D12, D13, D14, D15, D16, D17: LED; LED_0805_2012Metric
J1: Conn_01x09; PinHeader_1x09_P2.54mm_Vertical
J2: Conn_01x08; PinHeader_1x08_P2.54mm_Vertical
J3: Conn_01x16; PinHeader_1x16_P2.54mm_Vertical
R1, R2, R3, R4, R5, R6, R7, R8, R9, R10, R11, R12, R13, R14, R15, R16, R17, R18, R19, R20, R21, R22, R23: R_US; R_0805_2012Metric
U1, U2: IS61C5128AL-10KLI; SOJ-36_10.16x23.49mm_P1.27mm
U3, U4: 74LS173; TSSOP-16_4.4x5mm_P0.65mm
U5: 74LS157; TSSOP-16_4.4x5mm_P0.65mm
U6, U8: 74LS32; TSSOP-14_4.4x5mm_P0.65mm
U7: 74LS04; TSSOP-14_4.4x5mm_P0.65mm
U9: 28C256; DIP-28_W15.24mm_Socket

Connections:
+5V: C1.1, C2.1, C3.1, C4.1, J1.1, R17.2, R21.2, R22.2, R23.2, U1.9 (VDD), U1.27 (VDD), U2.9 (VDD), U2.27 (VDD), U3.16 (VCC), U4.16 (VCC), U5.16 (VCC), U6.14 (VCC), U7.14 (VCC), U8.14 (VCC), U9.27 (~WE), U9.28 (VCC)
/A0: J3.1, U1.1 (A0), U2.1 (A0), U9.10 (A0)
/A1: J3.2, U1.2 (A1), U2.2 (A1), U9.9 (A1)
/A2: J3.3, U1.3 (A2), U2.3 (A2), U9.8 (A2)
/A3: J3.4, U1.4 (A3), U2.4 (A3), U9.7 (A3)
/A4: J3.5, U1.5 (A4), U2.5 (A4), U9.6 (A4)
/A5: J3.6, U1.14 (A5), U2.14 (A5), U9.5 (A5)
/A6: J3.7, U1.15 (A6), U2.15 (A6), U9.4 (A6)
/A7: J3.8, U1.16 (A7), U2.16 (A7), U9.3 (A7)
/A8: J3.9, U1.17 (A8), U2.17 (A8), U9.25 (A8)
/A9: J3.10, U1.18 (A9), U2.18 (A9), U9.24 (A9)
/A10: J3.11, U1.20 (A10), U2.20 (A10), U9.21 (A10)
/A11: J3.12, U1.21 (A11), U2.21 (A11), U9.23 (A11)
/A12: J3.13, U1.22 (A12), U2.22 (A12), U9.2 (A12)
/A13: J3.14, U1.23 (A13), U2.23 (A13), U9.26 (A13)
/A14: J3.15, U1.24 (A14), U2.24 (A14), U9.1 (A14)
/A15: J3.16, U1.32 (A15), U2.32 (A15), U6.1
/A16: U1.33 (A16), U2.33 (A16), U5.4 (Za), U6.2
/A17: U1.34 (A17), U2.34 (A17), U5.7 (Zb), U6.4
/A18: U1.35 (A18), U2.35 (A18), U5.9 (Zc), U6.5
/CS0: D13.2 (A), U3.3 (Q0), U5.2 (I0a)
/CS1: D12.2 (A), U3.4 (Q1), U5.5 (I0b)
/CS2: D11.2 (A), U3.5 (Q2), U5.11 (I0c)
/CS3: D10.2 (A), U3.6 (Q3), U5.14 (I0d)
/DS0: D16.2 (A), U4.3 (Q0), U5.3 (I1a)
/DS1: D15.2 (A), U4.4 (Q1), U5.6 (I1b)
/DS2: D14.2 (A), U4.5 (Q2), U5.10 (I1c)
/DS3: D17.2 (A), U4.6 (Q3), U5.13 (I1d)
/IO0: D1.2 (A), J2.8, U1.7 (I/O0), U2.7 (I/O0), U3.14 (D0), U4.14 (D0), U9.11 (D0)
/IO1: D2.2 (A), J2.7, U1.8 (I/O1), U2.8 (I/O1), U3.13 (D1), U4.13 (D1), U9.12 (D1)
/IO2: D3.2 (A), J2.6, U1.11 (I/O2), U2.11 (I/O2), U3.12 (D2), U4.12 (D2), U9.13 (D2)
/IO3: D4.2 (A), J2.5, U1.12 (I/O3), U2.12 (I/O3), U3.11 (D3), U4.11 (D3), U9.15 (D3)
/IO4: D5.2 (A), J2.4, U1.25 (I/O4), U2.25 (I/O4), U9.16 (D4)
/IO5: D6.2 (A), J2.3, U1.26 (I/O5), U2.26 (I/O5), U9.17 (D5)
/IO6: D7.2 (A), J2.2, U1.29 (I/O6), U2.29 (I/O6), U9.18 (D6)
/IO7: D8.2 (A), J2.1, U1.30 (I/O7), U2.30 (I/O7), U9.19 (D7)
/~RAM_CS: U5.12 (Zd), U6.12, U7.1, U8.1
/~ROM_EN: U6.11, U7.9, U9.20 (~CS)
CLOCK: J1.7, U3.7 (Cp), U4.7 (Cp)
GND: C1.2, C2.2, C3.2, C4.2, J1.2, R1.2, R2.2, R3.2, R4.2, R5.2, R6.2, R7.2, R8.2, R9.2, R10.2, R11.2, R12.2, R13.2, R14.2, R15.2, R16.2, R18.2, R19.2, R20.2, U1.10 (Gnd), U1.28 (Gnd), U2.10 (Gnd), U2.28 (Gnd), U3.1 (Oe1), U3.2 (Oe2), U3.8 (GND), U4.1 (Oe1), U4.2 (Oe2), U4.8 (GND), U5.8 (GND), U5.15 (E), U6.7 (GND), U7.7 (GND), U7.13, U8.7 (GND), U8.9, U8.10, U8.12, U8.13, U9.14 (GND)
MODE: D9.2 (A), J1.8, R18.1, U5.1 (S)
MR: J1.9, R10.1, U3.15 (Mr), U4.15 (Mr)
unnamed: D1.1 (K), R1.1
unnamed: D2.1 (K), R2.1
unnamed: D3.1 (K), R3.1
unnamed: D4.1 (K), R4.1
unnamed: D5.1 (K), R5.1
unnamed: D6.1 (K), R6.1
unnamed: D7.1 (K), R7.1
unnamed: D8.1 (K), R8.1
unnamed: D9.1 (K), R9.1
unnamed: D10.1 (K), R19.1
unnamed: D11.1 (K), R11.1
unnamed: D12.1 (K), R12.1
unnamed: D13.1 (K), R13.1
unnamed: D14.1 (K), R14.1
unnamed: D15.1 (K), R15.1
unnamed: D16.1 (K), R16.1
unnamed: D17.1 (K), R20.1
unnamed: U1.6 (~CE), U8.3
unnamed: U2.6 (~CE), U7.2
unnamed: U6.3, U6.9
unnamed: U6.6, U6.10
unnamed: U6.8, U6.13
unnamed: U7.8, U8.2
~CS_IN: J1.5, R21.1, U3.9 (E1), U3.10 (E2)
~DS_IN: J1.6, R17.1, U4.9 (E1), U4.10 (E2)
~OE: J1.4, R22.1, U1.31 (~OE), U2.31 (~OE), U9.22 (~OE)
~WE: J1.3, R23.1, U1.13 (~WE), U2.13 (~WE)

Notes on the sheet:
CONNECTIONS
RAM (Low)
Code Segment Reg.
Data Segment Reg.
Segment MUX
Data I/O LEDs
RAM (High)
Indicator LEDs
Code Segment This is default active. It stays active when the CPU is fetching the next instruction to be decoded.
Data Segment This is default inactive. It is active when the CPU is either reading or writing to memory. ie. MOV $1:f733, #55 ie. MOV a, $0:f733
MUX When ~MODE~ line is set to: LOW (default) it will be using the values from Cs for the ~CE~ and A16..A18 lines HIGH (default) it will be using the values from Ds for the ~CE~ and A16..A18 lines
ROM
If A[15..18] are all LOW, and ~RAM_CS~ is LOW, then Enable ROM is LOW which makes ROM active. Same, if any A[15..18] or ~RAM_CS~ is HIGH, then ROM is disabled
ROM Enable
Unused Gates
Logic Power
